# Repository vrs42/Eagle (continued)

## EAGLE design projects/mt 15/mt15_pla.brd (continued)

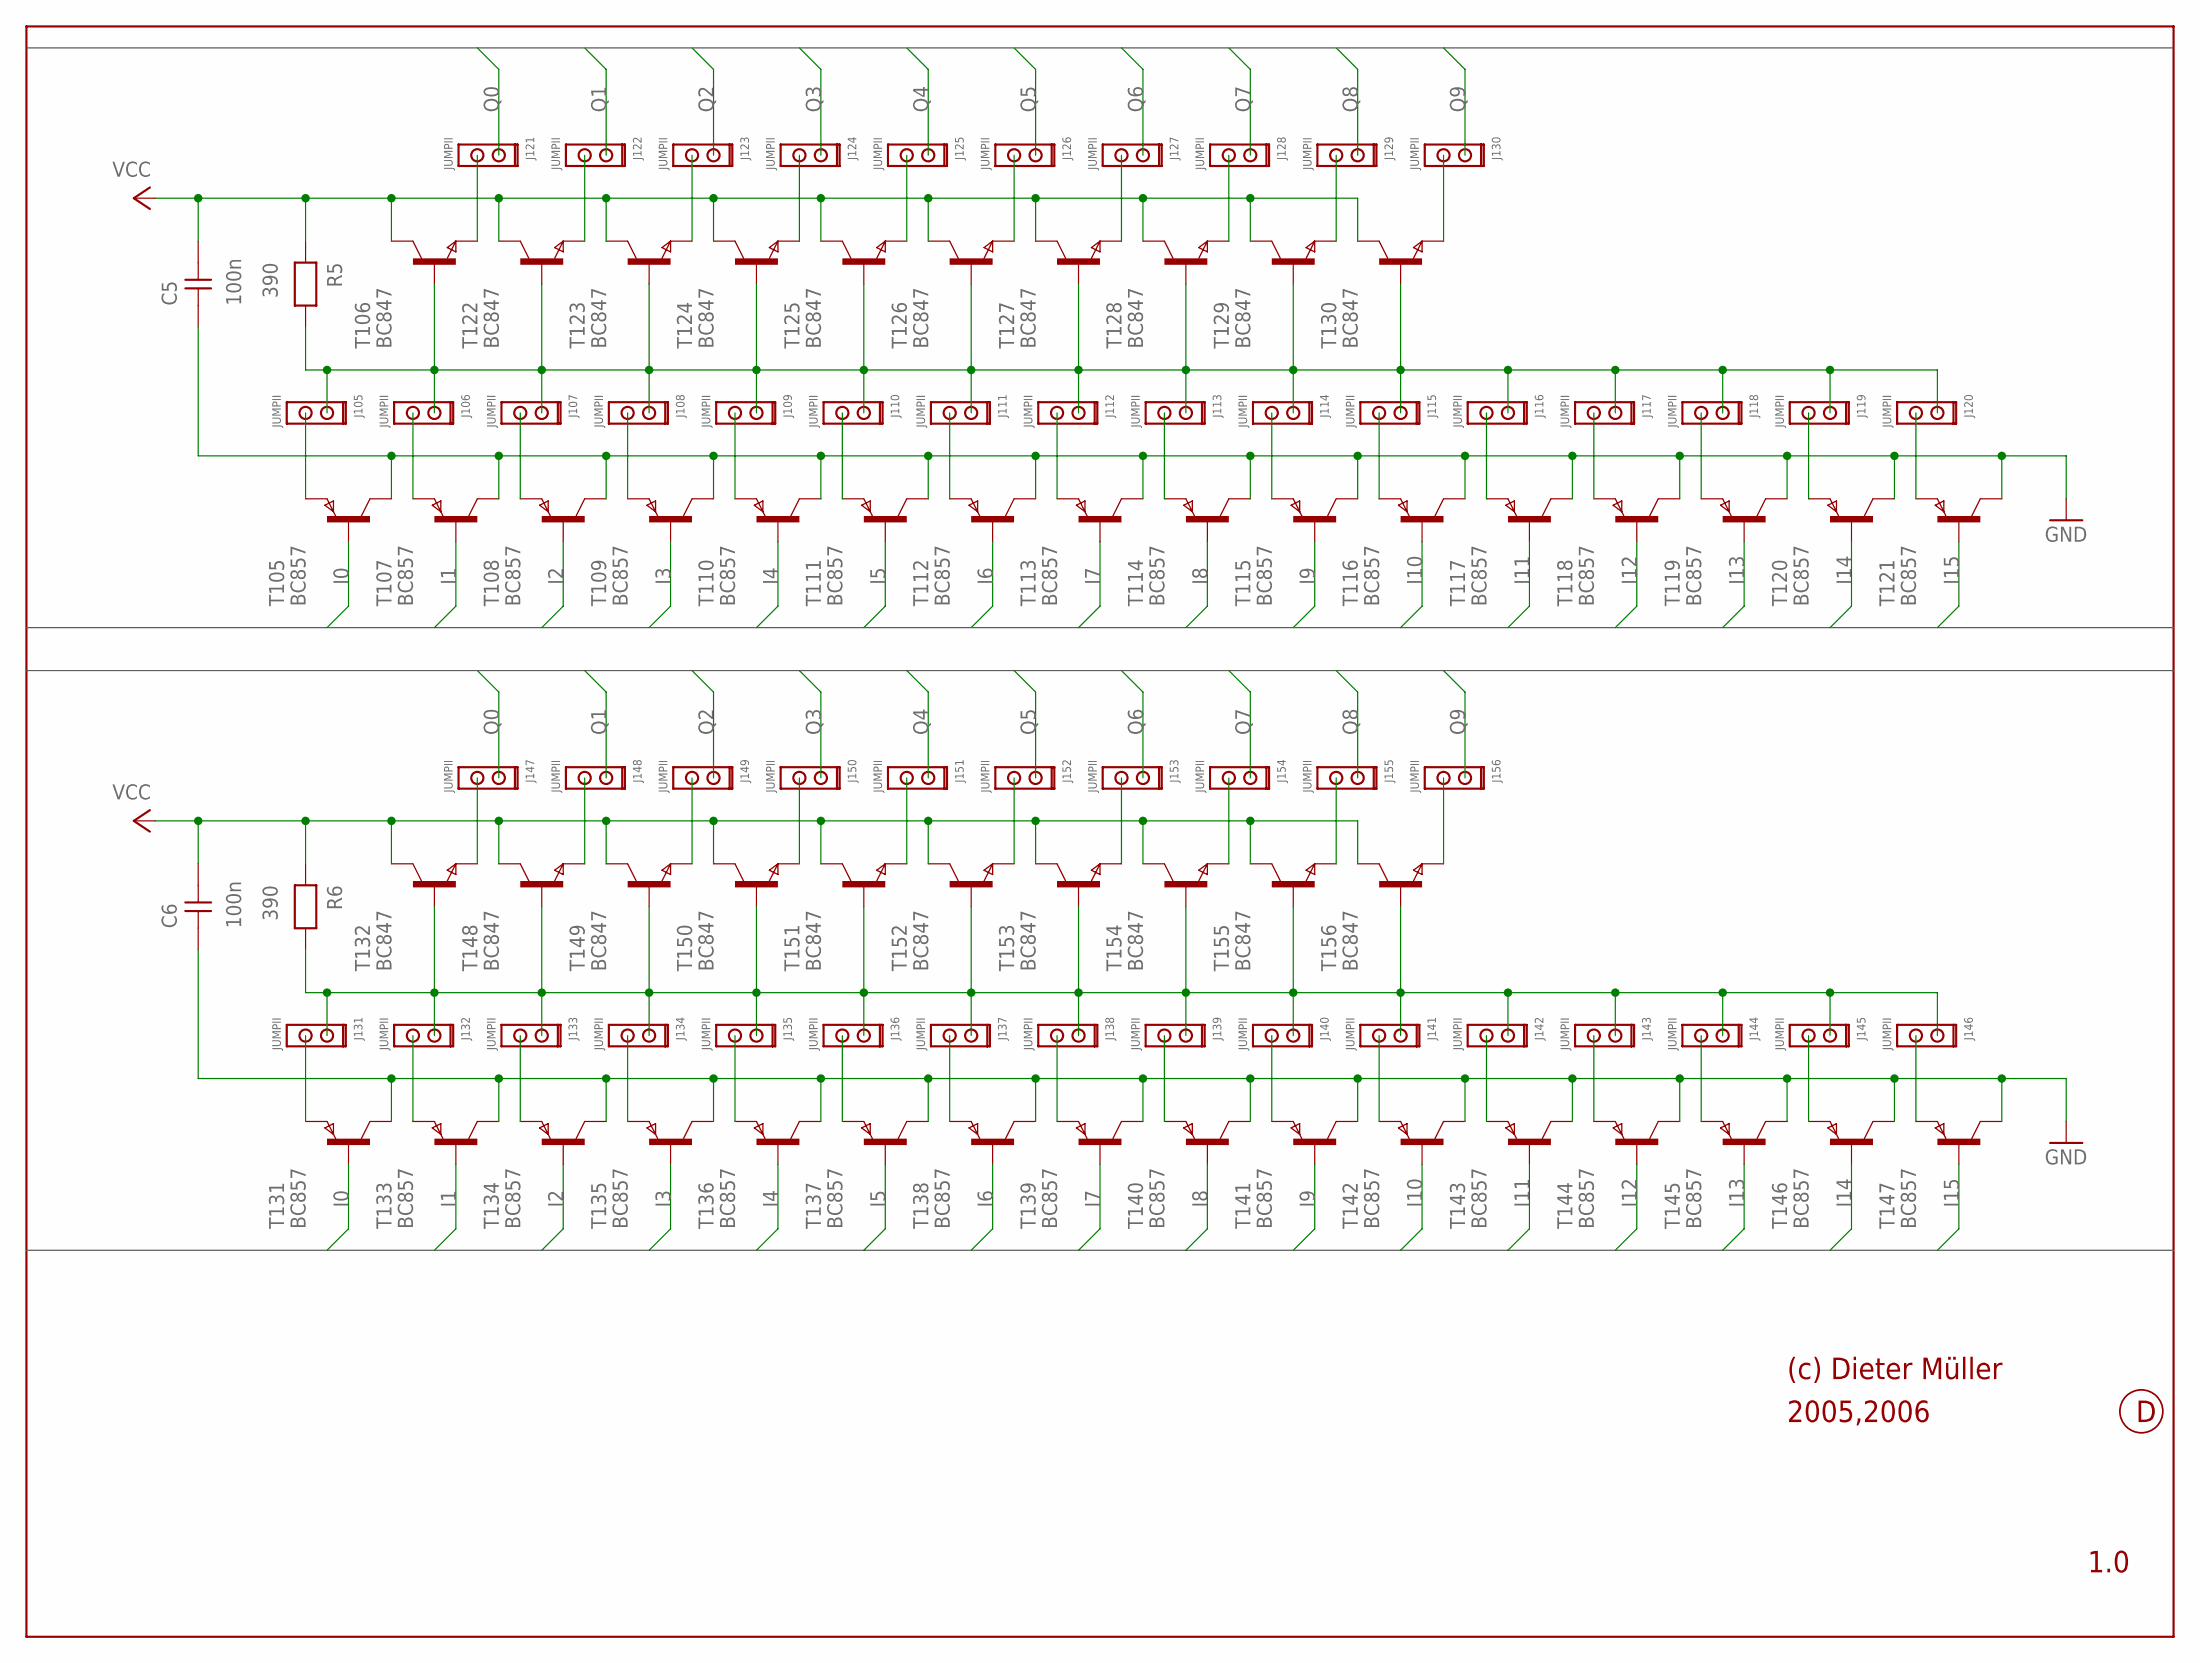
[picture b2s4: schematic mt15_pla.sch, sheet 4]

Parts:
C5, C6: 100n; 0204
J105, J106, J107, J108, J109, J110, J111, J112, J113, J114, J115, J116, J117, J118, J119, J120, J121, J122, J123, J124, J125, J126, J127, J128, J129, J130, J131, J132, J133, J134, J135, J136, J137, J138, J139, J140, J141, J142, J143, J144, J145, J146, J147, J148, J149, J150, J151, J152, J153, J154, J155, J156: JUMPII
R5, R6: 390; 0204
T105, T107, T108, T109, T110, T111, T112, T113, T114, T115, T116, T117, T118, T119, T120, T121, T131, T133, T134, T135, T136, T137, T138, T139, T140, T141, T142, T143, T144, T145, T146, T147: BC857; SOT-23
T106, T122, T123, T124, T125, T126, T127, T128, T129, T130, T132, T148, T149, T150, T151, T152, T153, T154, T155, T156: BC847; SOT-23

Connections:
GND: C5.1, C6.1, T105.3 (C), T107.3 (C), T108.3 (C), T109.3 (C), T110.3 (C), T111.3 (C), T112.3 (C), T113.3 (C), T114.3 (C), T115.3 (C), T116.3 (C), T117.3 (C), T118.3 (C), T119.3 (C), T120.3 (C), T121.3 (C), T131.3 (C), T133.3 (C), T134.3 (C), T135.3 (C), T136.3 (C), T137.3 (C), T138.3 (C), T139.3 (C), T140.3 (C), T141.3 (C), T142.3 (C), T143.3 (C), T144.3 (C), T145.3 (C), T146.3 (C), T147.3 (C); also elsewhere on the board
I0: T105.2 (B), T131.2 (B); also elsewhere on the board
I1: T107.2 (B), T133.2 (B); also elsewhere on the board
I2: T108.2 (B), T134.2 (B); also elsewhere on the board
I3: T109.2 (B), T135.2 (B); also elsewhere on the board
I4: T110.2 (B), T136.2 (B); also elsewhere on the board
I5: T111.2 (B), T137.2 (B); also elsewhere on the board
I6: T112.2 (B), T138.2 (B); also elsewhere on the board
I7: T113.2 (B), T139.2 (B); also elsewhere on the board
I8: T114.2 (B), T140.2 (B); also elsewhere on the board
I9: T115.2 (B), T141.2 (B); also elsewhere on the board
I10: T116.2 (B), T142.2 (B); also elsewhere on the board
I11: T117.2 (B), T143.2 (B); also elsewhere on the board
I12: T118.2 (B), T144.2 (B); also elsewhere on the board
I13: T119.2 (B), T145.2 (B); also elsewhere on the board
I14: T120.2 (B), T146.2 (B); also elsewhere on the board
I15: T121.2 (B), T147.2 (B); also elsewhere on the board
unnamed: J105.2, T105.1 (E)
unnamed: J106.2, T107.1 (E)
unnamed: J107.2, T108.1 (E)
unnamed: J105.1, J106.1, J107.1, J108.1, J109.1, J110.1, J111.1, J112.1, J113.1, J114.1, J115.1, J116.1, J117.1, J118.1, J119.1, J120.1, R5.2, T106.2 (B), T122.2 (B), T123.2 (B), T124.2 (B), T125.2 (B), T126.2 (B), T127.2 (B), T128.2 (B), T129.2 (B), T130.2 (B)
unnamed: J120.2, T121.1 (E)
unnamed: J119.2, T120.1 (E)
unnamed: J118.2, T119.1 (E)
unnamed: J117.2, T118.1 (E)
unnamed: J116.2, T117.1 (E)
unnamed: J110.2, T111.1 (E)
unnamed: J109.2, T110.1 (E)
unnamed: J108.2, T109.1 (E)
unnamed: J111.2, T112.1 (E)
unnamed: J112.2, T113.1 (E)
unnamed: J113.2, T114.1 (E)
unnamed: J114.2, T115.1 (E)
unnamed: J115.2, T116.1 (E)
unnamed: J130.2, T130.1 (E)
unnamed: J121.2, T106.1 (E)
unnamed: J122.2, T122.1 (E)
unnamed: J123.2, T123.1 (E)
unnamed: J124.2, T124.1 (E)
unnamed: J125.2, T125.1 (E)
unnamed: J126.2, T126.1 (E)
unnamed: J127.2, T127.1 (E)
unnamed: J128.2, T128.1 (E)
unnamed: J129.2, T129.1 (E)
unnamed: J131.2, T131.1 (E)
unnamed: J132.2, T133.1 (E)
unnamed: J133.2, T134.1 (E)
unnamed: J131.1, J132.1, J133.1, J134.1, J135.1, J136.1, J137.1, J138.1, J139.1, J140.1, J141.1, J142.1, J143.1, J144.1, J145.1, J146.1, R6.2, T132.2 (B), T148.2 (B), T149.2 (B), T150.2 (B), T151.2 (B), T152.2 (B), T153.2 (B), T154.2 (B), T155.2 (B), T156.2 (B)
unnamed: J146.2, T147.1 (E)
unnamed: J145.2, T146.1 (E)
unnamed: J144.2, T145.1 (E)
unnamed: J143.2, T144.1 (E)
unnamed: J142.2, T143.1 (E)
unnamed: J136.2, T137.1 (E)
unnamed: J135.2, T136.1 (E)
unnamed: J134.2, T135.1 (E)
unnamed: J137.2, T138.1 (E)
unnamed: J138.2, T139.1 (E)
unnamed: J139.2, T140.1 (E)
unnamed: J140.2, T141.1 (E)
unnamed: J141.2, T142.1 (E)
unnamed: J156.2, T156.1 (E)
unnamed: J147.2, T132.1 (E)
unnamed: J148.2, T148.1 (E)
unnamed: J149.2, T149.1 (E)
unnamed: J150.2, T150.1 (E)
unnamed: J151.2, T151.1 (E)
unnamed: J152.2, T152.1 (E)
unnamed: J153.2, T153.1 (E)
unnamed: J154.2, T154.1 (E)
unnamed: J155.2, T155.1 (E)
Q0: J121.1, J147.1; also elsewhere on the board
Q1: J122.1, J148.1; also elsewhere on the board
Q2: J123.1, J149.1; also elsewhere on the board
Q3: J124.1, J150.1; also elsewhere on the board
Q4: J125.1, J151.1; also elsewhere on the board
Q5: J126.1, J152.1; also elsewhere on the board
Q6: J127.1, J153.1; also elsewhere on the board
Q7: J128.1, J154.1; also elsewhere on the board
Q8: J129.1, J155.1; also elsewhere on the board
Q9: J130.1, J156.1; also elsewhere on the board
VCC: C5.2, C6.2, R5.1, R6.1, T106.3 (C), T122.3 (C), T123.3 (C), T124.3 (C), T125.3 (C), T126.3 (C), T127.3 (C), T128.3 (C), T129.3 (C), T130.3 (C), T132.3 (C), T148.3 (C), T149.3 (C), T150.3 (C), T151.3 (C), T152.3 (C), T153.3 (C), T154.3 (C), T155.3 (C), T156.3 (C); also elsewhere on the board

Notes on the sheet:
(c) Dieter Müller
2005,2006
1.0

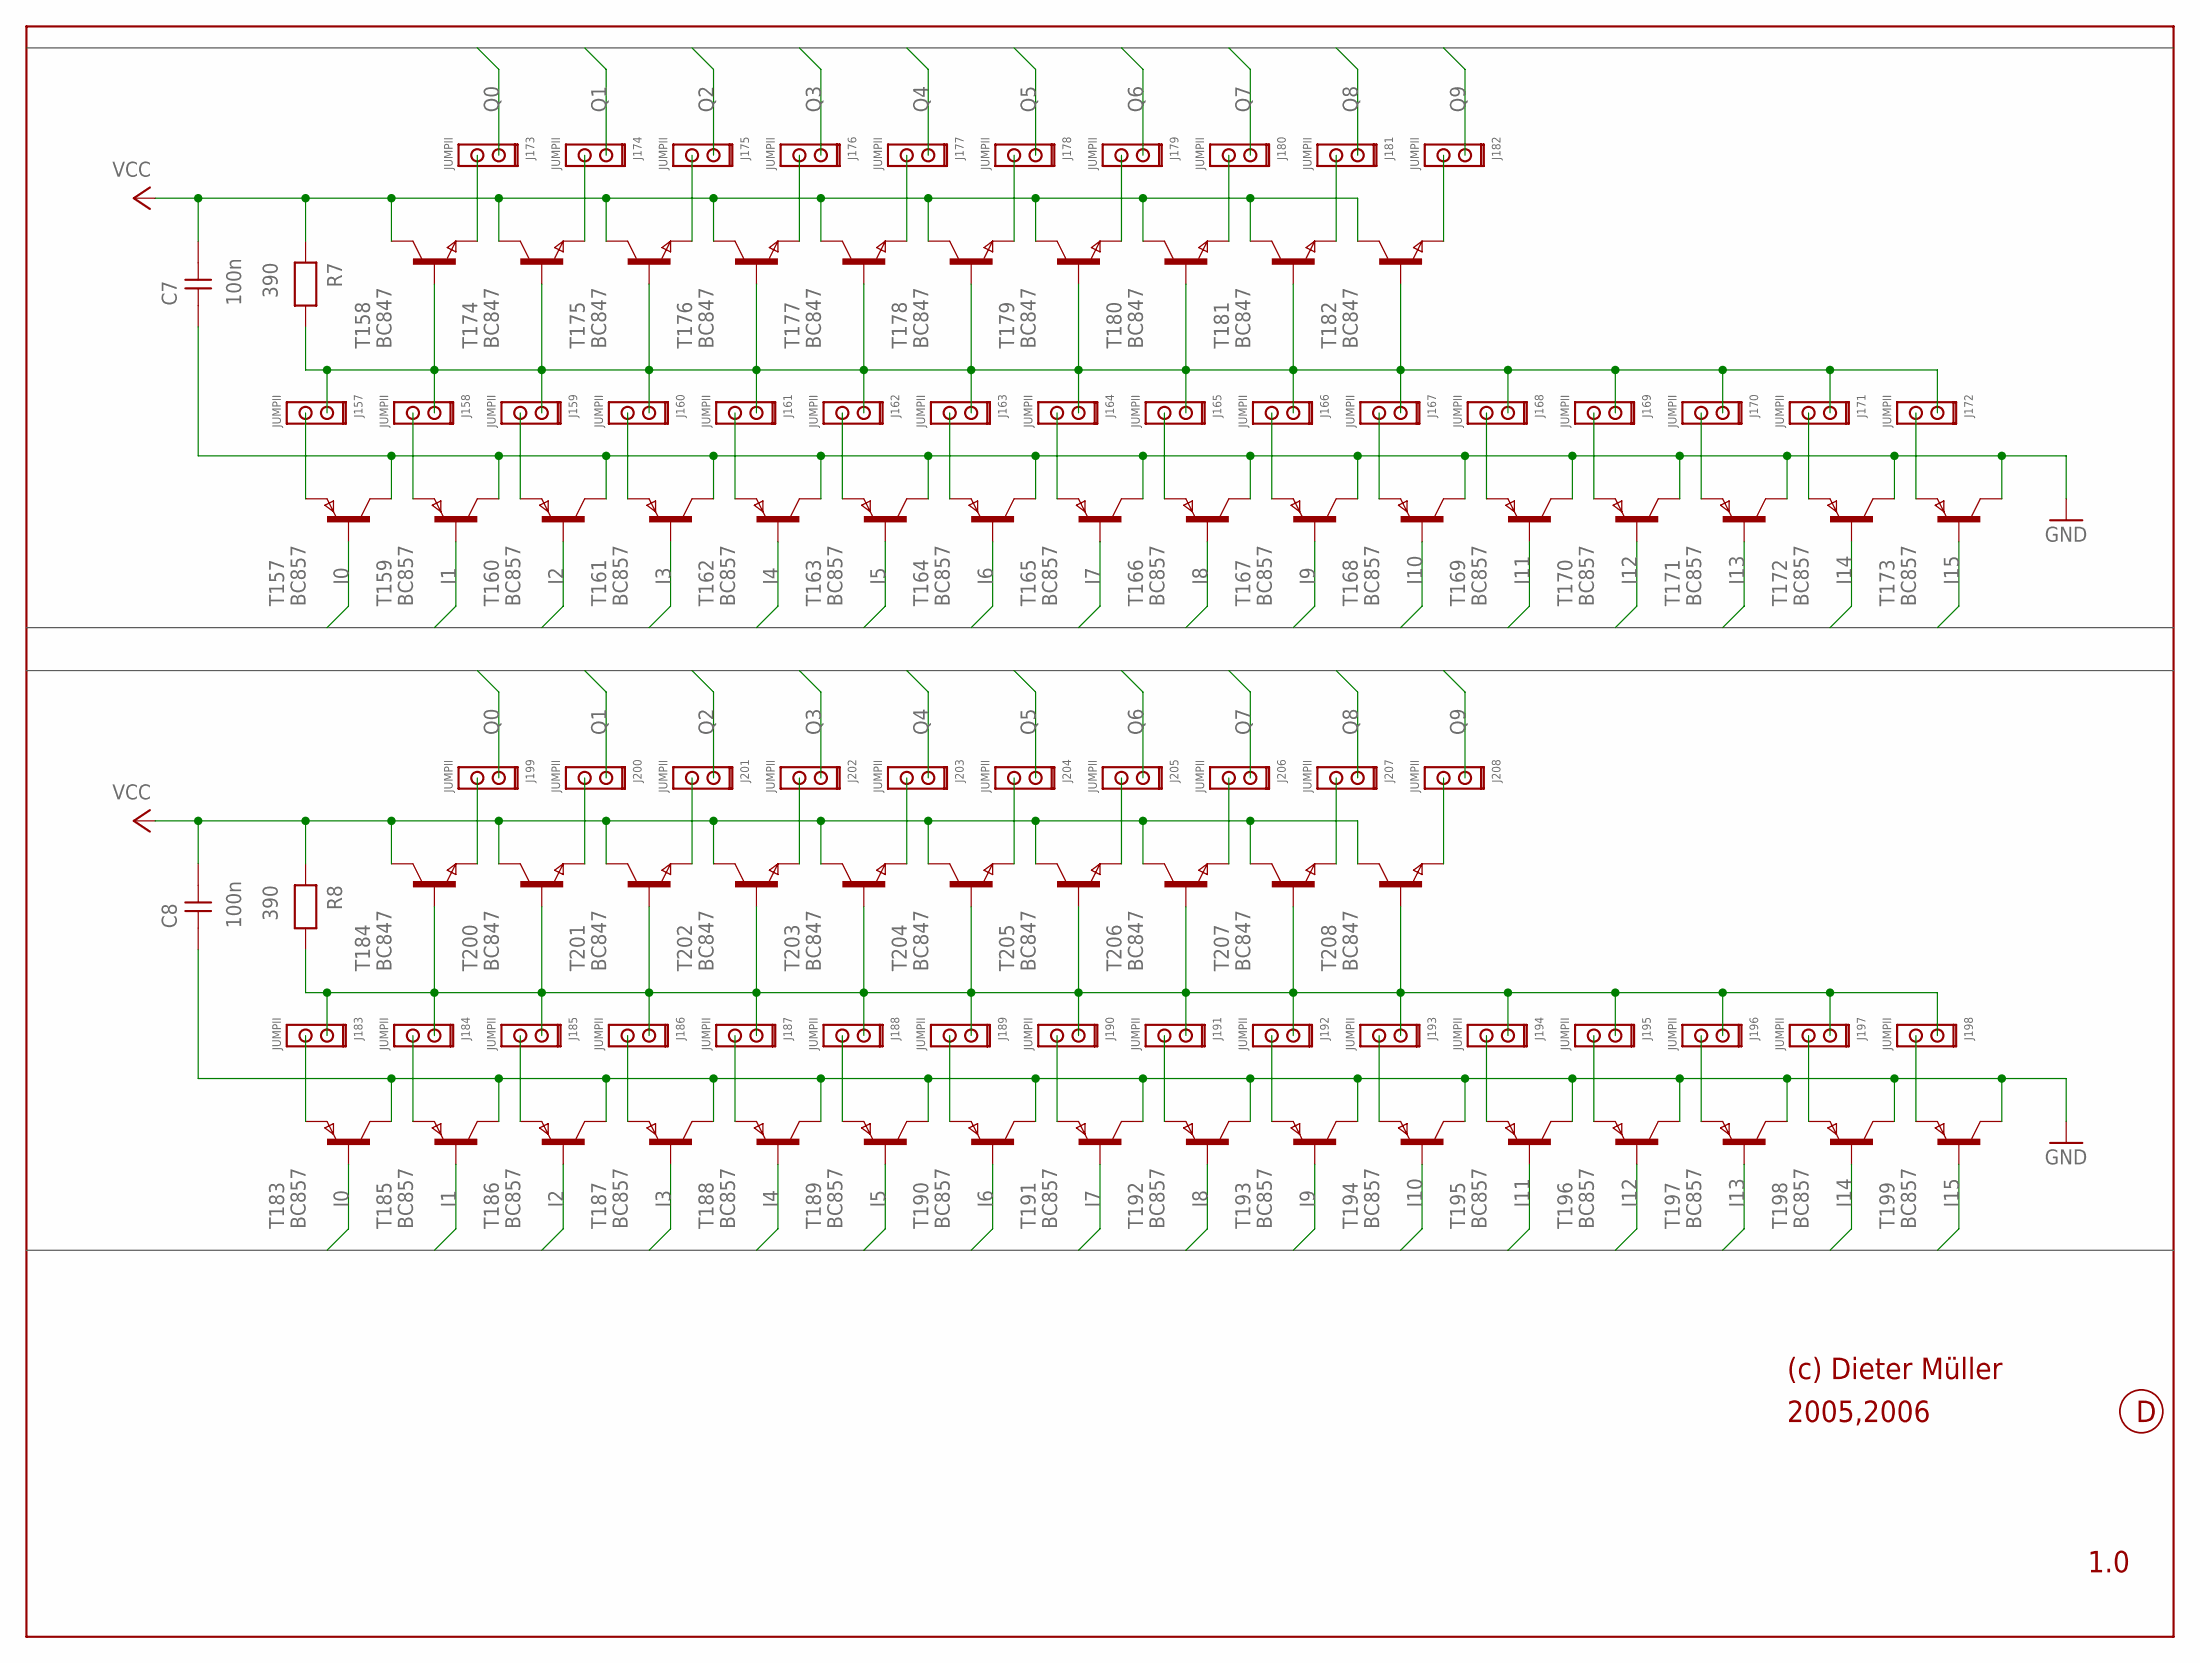
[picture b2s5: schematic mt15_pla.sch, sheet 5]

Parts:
C7, C8: 100n; 0204
J157, J158, J159, J160, J161, J162, J163, J164, J165, J166, J167, J168, J169, J170, J171, J172, J173, J174, J175, J176, J177, J178, J179, J180, J181, J182, J183, J184, J185, J186, J187, J188, J189, J190, J191, J192, J193, J194, J195, J196, J197, J198, J199, J200, J201, J202, J203, J204, J205, J206, J207, J208: JUMPII
R7, R8: 390; 0204
T157, T159, T160, T161, T162, T163, T164, T165, T166, T167, T168, T169, T170, T171, T172, T173, T183, T185, T186, T187, T188, T189, T190, T191, T192, T193, T194, T195, T196, T197, T198, T199: BC857; SOT-23
T158, T174, T175, T176, T177, T178, T179, T180, T181, T182, T184, T200, T201, T202, T203, T204, T205, T206, T207, T208: BC847; SOT-23

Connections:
GND: C7.1, C8.1, T157.3 (C), T159.3 (C), T160.3 (C), T161.3 (C), T162.3 (C), T163.3 (C), T164.3 (C), T165.3 (C), T166.3 (C), T167.3 (C), T168.3 (C), T169.3 (C), T170.3 (C), T171.3 (C), T172.3 (C), T173.3 (C), T183.3 (C), T185.3 (C), T186.3 (C), T187.3 (C), T188.3 (C), T189.3 (C), T190.3 (C), T191.3 (C), T192.3 (C), T193.3 (C), T194.3 (C), T195.3 (C), T196.3 (C), T197.3 (C), T198.3 (C), T199.3 (C); also elsewhere on the board
I0: T157.2 (B), T183.2 (B); also elsewhere on the board
I1: T159.2 (B), T185.2 (B); also elsewhere on the board
I2: T160.2 (B), T186.2 (B); also elsewhere on the board
I3: T161.2 (B), T187.2 (B); also elsewhere on the board
I4: T162.2 (B), T188.2 (B); also elsewhere on the board
I5: T163.2 (B), T189.2 (B); also elsewhere on the board
I6: T164.2 (B), T190.2 (B); also elsewhere on the board
I7: T165.2 (B), T191.2 (B); also elsewhere on the board
I8: T166.2 (B), T192.2 (B); also elsewhere on the board
I9: T167.2 (B), T193.2 (B); also elsewhere on the board
I10: T168.2 (B), T194.2 (B); also elsewhere on the board
I11: T169.2 (B), T195.2 (B); also elsewhere on the board
I12: T170.2 (B), T196.2 (B); also elsewhere on the board
I13: T171.2 (B), T197.2 (B); also elsewhere on the board
I14: T172.2 (B), T198.2 (B); also elsewhere on the board
I15: T173.2 (B), T199.2 (B); also elsewhere on the board
unnamed: J157.2, T157.1 (E)
unnamed: J158.2, T159.1 (E)
unnamed: J159.2, T160.1 (E)
unnamed: J157.1, J158.1, J159.1, J160.1, J161.1, J162.1, J163.1, J164.1, J165.1, J166.1, J167.1, J168.1, J169.1, J170.1, J171.1, J172.1, R7.2, T158.2 (B), T174.2 (B), T175.2 (B), T176.2 (B), T177.2 (B), T178.2 (B), T179.2 (B), T180.2 (B), T181.2 (B), T182.2 (B)
unnamed: J172.2, T173.1 (E)
unnamed: J171.2, T172.1 (E)
unnamed: J170.2, T171.1 (E)
unnamed: J169.2, T170.1 (E)
unnamed: J168.2, T169.1 (E)
unnamed: J162.2, T163.1 (E)
unnamed: J161.2, T162.1 (E)
unnamed: J160.2, T161.1 (E)
unnamed: J163.2, T164.1 (E)
unnamed: J164.2, T165.1 (E)
unnamed: J165.2, T166.1 (E)
unnamed: J166.2, T167.1 (E)
unnamed: J167.2, T168.1 (E)
unnamed: J182.2, T182.1 (E)
unnamed: J173.2, T158.1 (E)
unnamed: J174.2, T174.1 (E)
unnamed: J175.2, T175.1 (E)
unnamed: J176.2, T176.1 (E)
unnamed: J177.2, T177.1 (E)
unnamed: J178.2, T178.1 (E)
unnamed: J179.2, T179.1 (E)
unnamed: J180.2, T180.1 (E)
unnamed: J181.2, T181.1 (E)
unnamed: J183.2, T183.1 (E)
unnamed: J184.2, T185.1 (E)
unnamed: J185.2, T186.1 (E)
unnamed: J183.1, J184.1, J185.1, J186.1, J187.1, J188.1, J189.1, J190.1, J191.1, J192.1, J193.1, J194.1, J195.1, J196.1, J197.1, J198.1, R8.2, T184.2 (B), T200.2 (B), T201.2 (B), T202.2 (B), T203.2 (B), T204.2 (B), T205.2 (B), T206.2 (B), T207.2 (B), T208.2 (B)
unnamed: J198.2, T199.1 (E)
unnamed: J197.2, T198.1 (E)
unnamed: J196.2, T197.1 (E)
unnamed: J195.2, T196.1 (E)
unnamed: J194.2, T195.1 (E)
unnamed: J188.2, T189.1 (E)
unnamed: J187.2, T188.1 (E)
unnamed: J186.2, T187.1 (E)
unnamed: J189.2, T190.1 (E)
unnamed: J190.2, T191.1 (E)
unnamed: J191.2, T192.1 (E)
unnamed: J192.2, T193.1 (E)
unnamed: J193.2, T194.1 (E)
unnamed: J208.2, T208.1 (E)
unnamed: J199.2, T184.1 (E)
unnamed: J200.2, T200.1 (E)
unnamed: J201.2, T201.1 (E)
unnamed: J202.2, T202.1 (E)
unnamed: J203.2, T203.1 (E)
unnamed: J204.2, T204.1 (E)
unnamed: J205.2, T205.1 (E)
unnamed: J206.2, T206.1 (E)
unnamed: J207.2, T207.1 (E)
Q0: J173.1, J199.1; also elsewhere on the board
Q1: J174.1, J200.1; also elsewhere on the board
Q2: J175.1, J201.1; also elsewhere on the board
Q3: J176.1, J202.1; also elsewhere on the board
Q4: J177.1, J203.1; also elsewhere on the board
Q5: J178.1, J204.1; also elsewhere on the board
Q6: J179.1, J205.1; also elsewhere on the board
Q7: J180.1, J206.1; also elsewhere on the board
Q8: J181.1, J207.1; also elsewhere on the board
Q9: J182.1, J208.1; also elsewhere on the board
VCC: C7.2, C8.2, R7.1, R8.1, T158.3 (C), T174.3 (C), T175.3 (C), T176.3 (C), T177.3 (C), T178.3 (C), T179.3 (C), T180.3 (C), T181.3 (C), T182.3 (C), T184.3 (C), T200.3 (C), T201.3 (C), T202.3 (C), T203.3 (C), T204.3 (C), T205.3 (C), T206.3 (C), T207.3 (C), T208.3 (C); also elsewhere on the board

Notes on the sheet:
(c) Dieter Müller
2005,2006
1.0

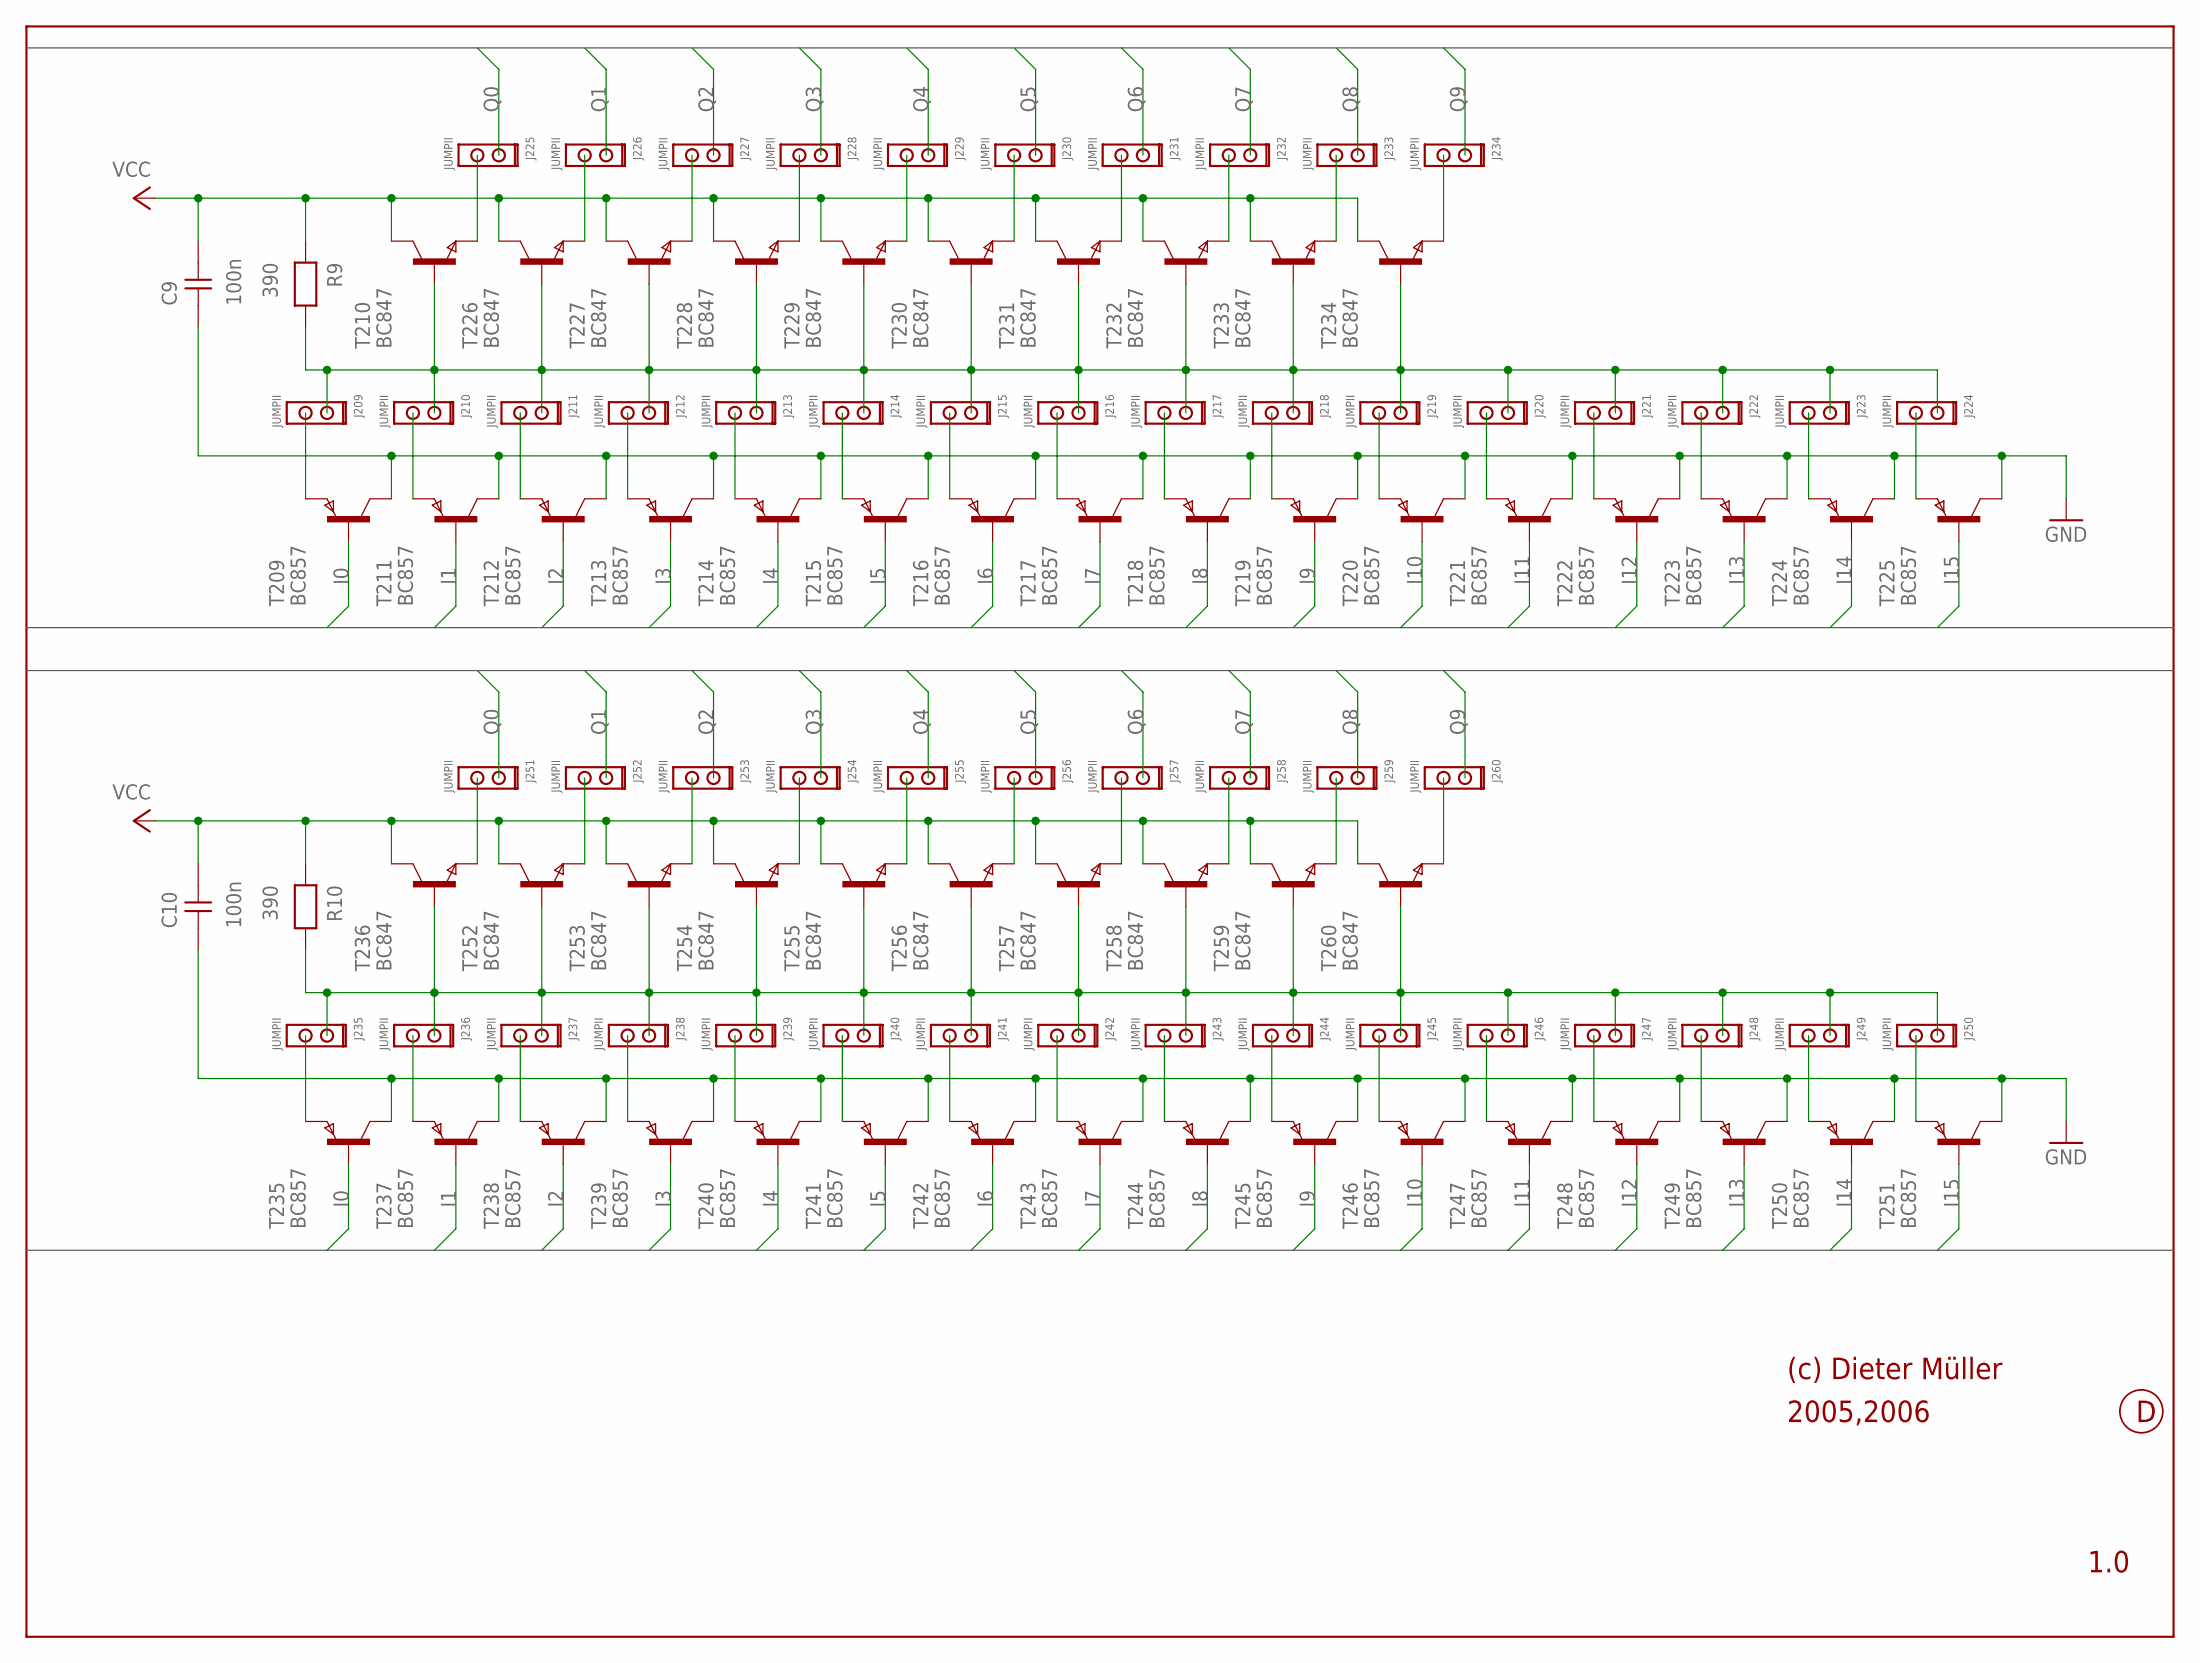
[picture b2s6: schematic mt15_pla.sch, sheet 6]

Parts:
C9, C10: 100n; 0204
J209, J210, J211, J212, J213, J214, J215, J216, J217, J218, J219, J220, J221, J222, J223, J224, J225, J226, J227, J228, J229, J230, J231, J232, J233, J234, J235, J236, J237, J238, J239, J240, J241, J242, J243, J244, J245, J246, J247, J248, J249, J250, J251, J252, J253, J254, J255, J256, J257, J258, J259, J260: JUMPII
R9, R10: 390; 0204
T209, T211, T212, T213, T214, T215, T216, T217, T218, T219, T220, T221, T222, T223, T224, T225, T235, T237, T238, T239, T240, T241, T242, T243, T244, T245, T246, T247, T248, T249, T250, T251: BC857; SOT-23
T210, T226, T227, T228, T229, T230, T231, T232, T233, T234, T236, T252, T253, T254, T255, T256, T257, T258, T259, T260: BC847; SOT-23

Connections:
GND: C9.1, C10.1, T209.3 (C), T211.3 (C), T212.3 (C), T213.3 (C), T214.3 (C), T215.3 (C), T216.3 (C), T217.3 (C), T218.3 (C), T219.3 (C), T220.3 (C), T221.3 (C), T222.3 (C), T223.3 (C), T224.3 (C), T225.3 (C), T235.3 (C), T237.3 (C), T238.3 (C), T239.3 (C), T240.3 (C), T241.3 (C), T242.3 (C), T243.3 (C), T244.3 (C), T245.3 (C), T246.3 (C), T247.3 (C), T248.3 (C), T249.3 (C), T250.3 (C), T251.3 (C); also elsewhere on the board
I0: T209.2 (B), T235.2 (B); also elsewhere on the board
I1: T211.2 (B), T237.2 (B); also elsewhere on the board
I2: T212.2 (B), T238.2 (B); also elsewhere on the board
I3: T213.2 (B), T239.2 (B); also elsewhere on the board
I4: T214.2 (B), T240.2 (B); also elsewhere on the board
I5: T215.2 (B), T241.2 (B); also elsewhere on the board
I6: T216.2 (B), T242.2 (B); also elsewhere on the board
I7: T217.2 (B), T243.2 (B); also elsewhere on the board
I8: T218.2 (B), T244.2 (B); also elsewhere on the board
I9: T219.2 (B), T245.2 (B); also elsewhere on the board
I10: T220.2 (B), T246.2 (B); also elsewhere on the board
I11: T221.2 (B), T247.2 (B); also elsewhere on the board
I12: T222.2 (B), T248.2 (B); also elsewhere on the board
I13: T223.2 (B), T249.2 (B); also elsewhere on the board
I14: T224.2 (B), T250.2 (B); also elsewhere on the board
I15: T225.2 (B), T251.2 (B); also elsewhere on the board
unnamed: J209.2, T209.1 (E)
unnamed: J210.2, T211.1 (E)
unnamed: J211.2, T212.1 (E)
unnamed: J209.1, J210.1, J211.1, J212.1, J213.1, J214.1, J215.1, J216.1, J217.1, J218.1, J219.1, J220.1, J221.1, J222.1, J223.1, J224.1, R9.2, T210.2 (B), T226.2 (B), T227.2 (B), T228.2 (B), T229.2 (B), T230.2 (B), T231.2 (B), T232.2 (B), T233.2 (B), T234.2 (B)
unnamed: J224.2, T225.1 (E)
unnamed: J223.2, T224.1 (E)
unnamed: J222.2, T223.1 (E)
unnamed: J221.2, T222.1 (E)
unnamed: J220.2, T221.1 (E)
unnamed: J214.2, T215.1 (E)
unnamed: J213.2, T214.1 (E)
unnamed: J212.2, T213.1 (E)
unnamed: J215.2, T216.1 (E)
unnamed: J216.2, T217.1 (E)
unnamed: J217.2, T218.1 (E)
unnamed: J218.2, T219.1 (E)
unnamed: J219.2, T220.1 (E)
unnamed: J234.2, T234.1 (E)
unnamed: J225.2, T210.1 (E)
unnamed: J226.2, T226.1 (E)
unnamed: J227.2, T227.1 (E)
unnamed: J228.2, T228.1 (E)
unnamed: J229.2, T229.1 (E)
unnamed: J230.2, T230.1 (E)
unnamed: J231.2, T231.1 (E)
unnamed: J232.2, T232.1 (E)
unnamed: J233.2, T233.1 (E)
unnamed: J235.2, T235.1 (E)
unnamed: J236.2, T237.1 (E)
unnamed: J237.2, T238.1 (E)
unnamed: J235.1, J236.1, J237.1, J238.1, J239.1, J240.1, J241.1, J242.1, J243.1, J244.1, J245.1, J246.1, J247.1, J248.1, J249.1, J250.1, R10.2, T236.2 (B), T252.2 (B), T253.2 (B), T254.2 (B), T255.2 (B), T256.2 (B), T257.2 (B), T258.2 (B), T259.2 (B), T260.2 (B)
unnamed: J250.2, T251.1 (E)
unnamed: J249.2, T250.1 (E)
unnamed: J248.2, T249.1 (E)
unnamed: J247.2, T248.1 (E)
unnamed: J246.2, T247.1 (E)
unnamed: J240.2, T241.1 (E)
unnamed: J239.2, T240.1 (E)
unnamed: J238.2, T239.1 (E)
unnamed: J241.2, T242.1 (E)
unnamed: J242.2, T243.1 (E)
unnamed: J243.2, T244.1 (E)
unnamed: J244.2, T245.1 (E)
unnamed: J245.2, T246.1 (E)
unnamed: J260.2, T260.1 (E)
unnamed: J251.2, T236.1 (E)
unnamed: J252.2, T252.1 (E)
unnamed: J253.2, T253.1 (E)
unnamed: J254.2, T254.1 (E)
unnamed: J255.2, T255.1 (E)
unnamed: J256.2, T256.1 (E)
unnamed: J257.2, T257.1 (E)
unnamed: J258.2, T258.1 (E)
unnamed: J259.2, T259.1 (E)
Q0: J225.1, J251.1; also elsewhere on the board
Q1: J226.1, J252.1; also elsewhere on the board
Q2: J227.1, J253.1; also elsewhere on the board
Q3: J228.1, J254.1; also elsewhere on the board
Q4: J229.1, J255.1; also elsewhere on the board
Q5: J230.1, J256.1; also elsewhere on the board
Q6: J231.1, J257.1; also elsewhere on the board
Q7: J232.1, J258.1; also elsewhere on the board
Q8: J233.1, J259.1; also elsewhere on the board
Q9: J234.1, J260.1; also elsewhere on the board
VCC: C9.2, C10.2, R9.1, R10.1, T210.3 (C), T226.3 (C), T227.3 (C), T228.3 (C), T229.3 (C), T230.3 (C), T231.3 (C), T232.3 (C), T233.3 (C), T234.3 (C), T236.3 (C), T252.3 (C), T253.3 (C), T254.3 (C), T255.3 (C), T256.3 (C), T257.3 (C), T258.3 (C), T259.3 (C), T260.3 (C); also elsewhere on the board

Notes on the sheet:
(c) Dieter Müller
2005,2006
1.0
